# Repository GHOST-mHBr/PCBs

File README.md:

# How To Use
Just open your desired folder

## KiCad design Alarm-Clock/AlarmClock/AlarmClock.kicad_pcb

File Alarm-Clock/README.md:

# PCB for Alarm-Clock project
You can find source code [here](github.com/GHOST-mHBr/https://github.com/GHOST-mHBr/AVR-Codes/tree/master/Atmega8%20Async%20Timer2%20Standard%20C%20time%20API)

# 3D views of the final PCB
## Perspective View

## Front View

## Back View

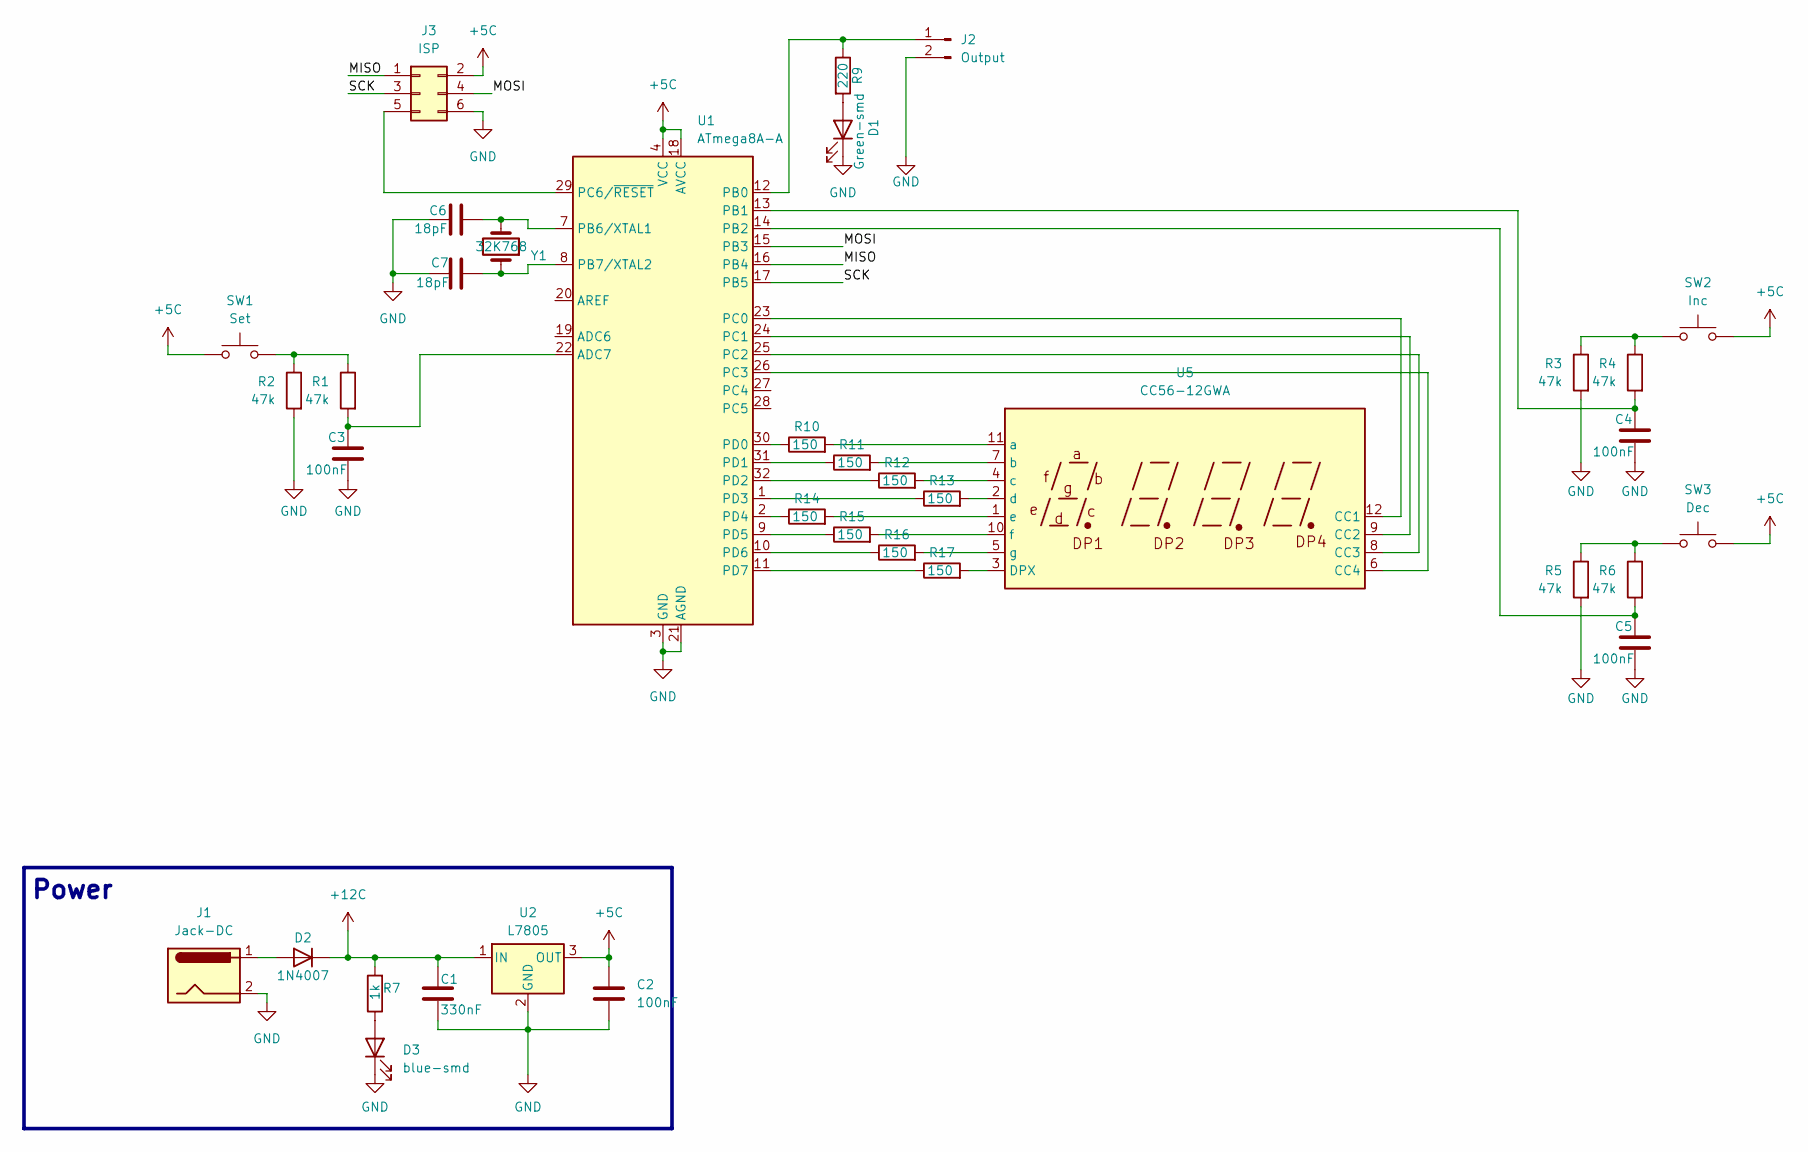
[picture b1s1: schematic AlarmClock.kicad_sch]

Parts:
C1: 330nF; C_0603_1608Metric
C2, C3, C4, C5: 100nF; C_0603_1608Metric
C6, C7: 18pF; C_0603_1608Metric
D1: Green-smd; LED_0805_2012Metric
D2: 1N4007; D_SMA
D3: blue-smd; LED_0603_1608Metric
J1: Jack-DC; BarrelJack_GCT_DCJ200-10-A_Horizontal
J2: Output; Molex_KK-254_AE-6410-02A_1x02_P2.54mm_Vertical
J3: ISP; IDC-Header_2x03_P2.54mm_Vertical
R1, R2, R3, R4, R5, R6: 47k; R_0603_1608Metric
R7: 1k; R_0603_1608Metric
R9: 220; R_0603_1608Metric
R10, R11, R12, R13, R14, R15, R16, R17: 150; R_0603_1608Metric
SW1: Set; Molex_KK-254_AE-6410-02A_1x02_P2.54mm_Vertical
SW2: Inc; Molex_KK-254_AE-6410-02A_1x02_P2.54mm_Vertical
SW3: Dec; Molex_KK-254_AE-6410-02A_1x02_P2.54mm_Vertical
U1: ATmega8A-A; TQFP-32_7x7mm_P0.8mm
U2: L7805; TO-220-3_Horizontal_TabDown
U5: CC56-12GWA
Y1: 32K768; Crystal_SMD_2012-2Pin_2.0x1.2mm

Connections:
+5C: C2.1, J3.2, SW1.1, SW2.1, SW3.1, U1.4 (VCC), U1.6 (VCC), U1.18 (AVCC), U2.3 (OUT)
+12C: C1.1, D2.1 (K), R7.2, U2.1 (IN)
/MISO: J3.1, U1.16 (PB4)
/MOSI: J3.4, U1.15 (PB3)
/SCK: J3.3, U1.17 (PB5)
GND: C1.2, C2.2, C3.2, C4.2, C5.2, C6.1, C7.1, D1.1 (K), D3.1 (K), J1.2, J2.2, J3.6, R2.2, R3.2, R5.2, U1.3 (GND), U1.5 (GND), U1.21 (AGND), U2.2 (GND)
unnamed: D1.2 (A), R9.2
unnamed: D2.2 (A), J1.1
unnamed: D3.2 (A), R7.1
unnamed: J2.1, R9.1, U1.12 (PB0)
unnamed: J3.5, U1.29 (PC6/~RESET)
unnamed: R1.1, R2.1, SW1.2
unnamed: R3.1, R4.1, SW2.2
unnamed: R5.1, R6.1, SW3.2
unnamed: C3.1, R1.2, U1.22 (ADC7)
unnamed: C4.1, R4.2, U1.13 (PB1)
unnamed: C5.1, R6.2, U1.14 (PB2)
unnamed: C6.2, U1.7 (PB6/XTAL1), Y1.2
unnamed: C7.2, U1.8 (PB7/XTAL2), Y1.1
unnamed: U1.23 (PC0), U5.12 (CC1)
unnamed: U1.24 (PC1), U5.9 (CC2)
unnamed: U1.25 (PC2), U5.8 (CC3)
unnamed: U1.26 (PC3), U5.6 (CC4)
unnamed: R10.1, U1.30 (PD0)
unnamed: R11.1, U1.31 (PD1)
unnamed: R12.1, U1.32 (PD2)
unnamed: R13.1, U1.1 (PD3)
unnamed: R14.1, U1.2 (PD4)
unnamed: R15.1, U1.9 (PD5)
unnamed: R16.1, U1.10 (PD6)
unnamed: R17.1, U1.11 (PD7)
unnamed: R17.2, U5.3 (DPX)
unnamed: R10.2, U5.11 (a)
unnamed: R11.2, U5.7 (b)
unnamed: R12.2, U5.4 (c)
unnamed: R13.2, U5.2 (d)
unnamed: R14.2, U5.1 (e)
unnamed: R15.2, U5.10 (f)
unnamed: R16.2, U5.5 (g)

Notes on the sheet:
Power

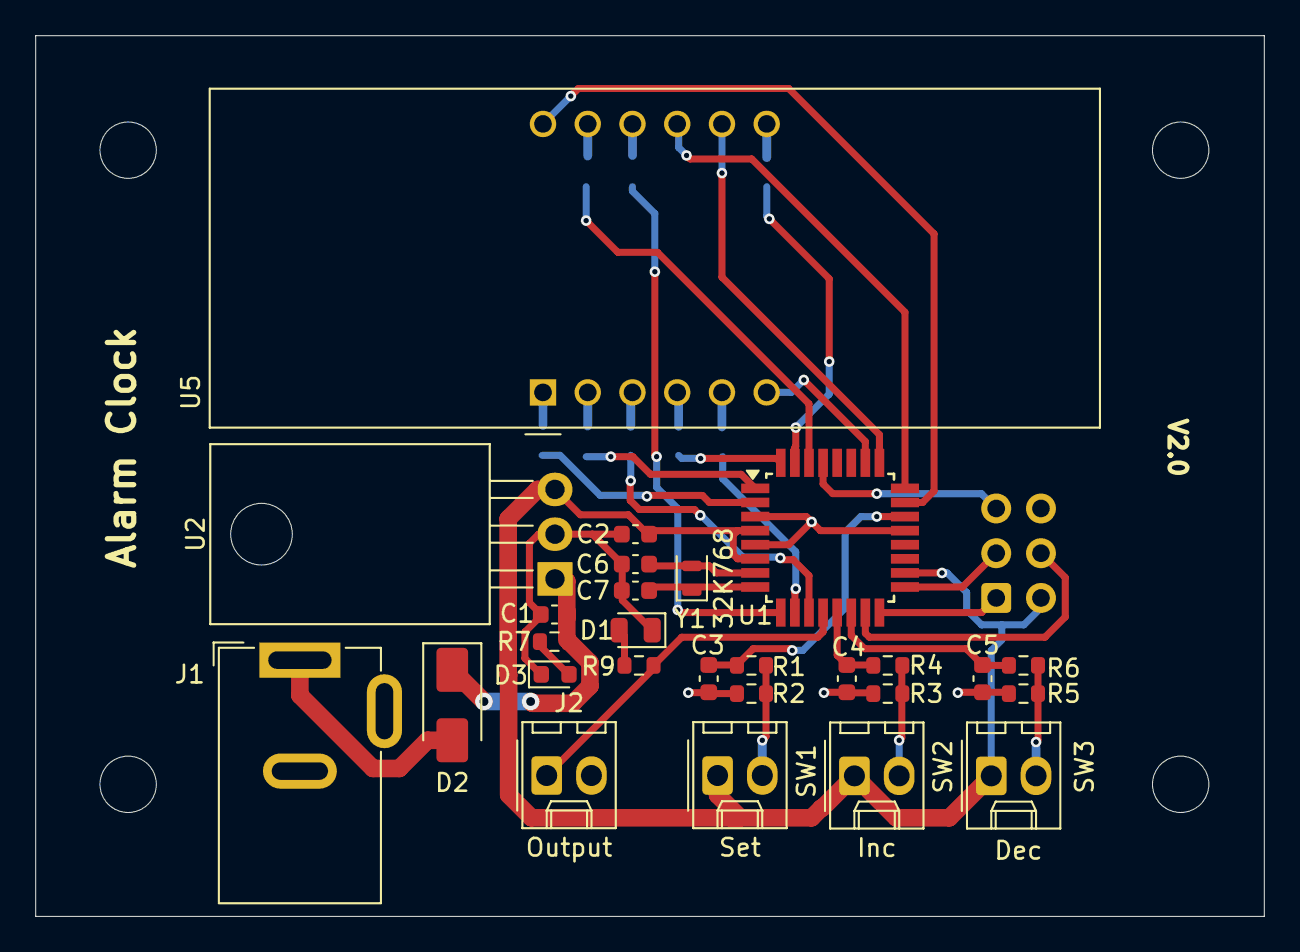
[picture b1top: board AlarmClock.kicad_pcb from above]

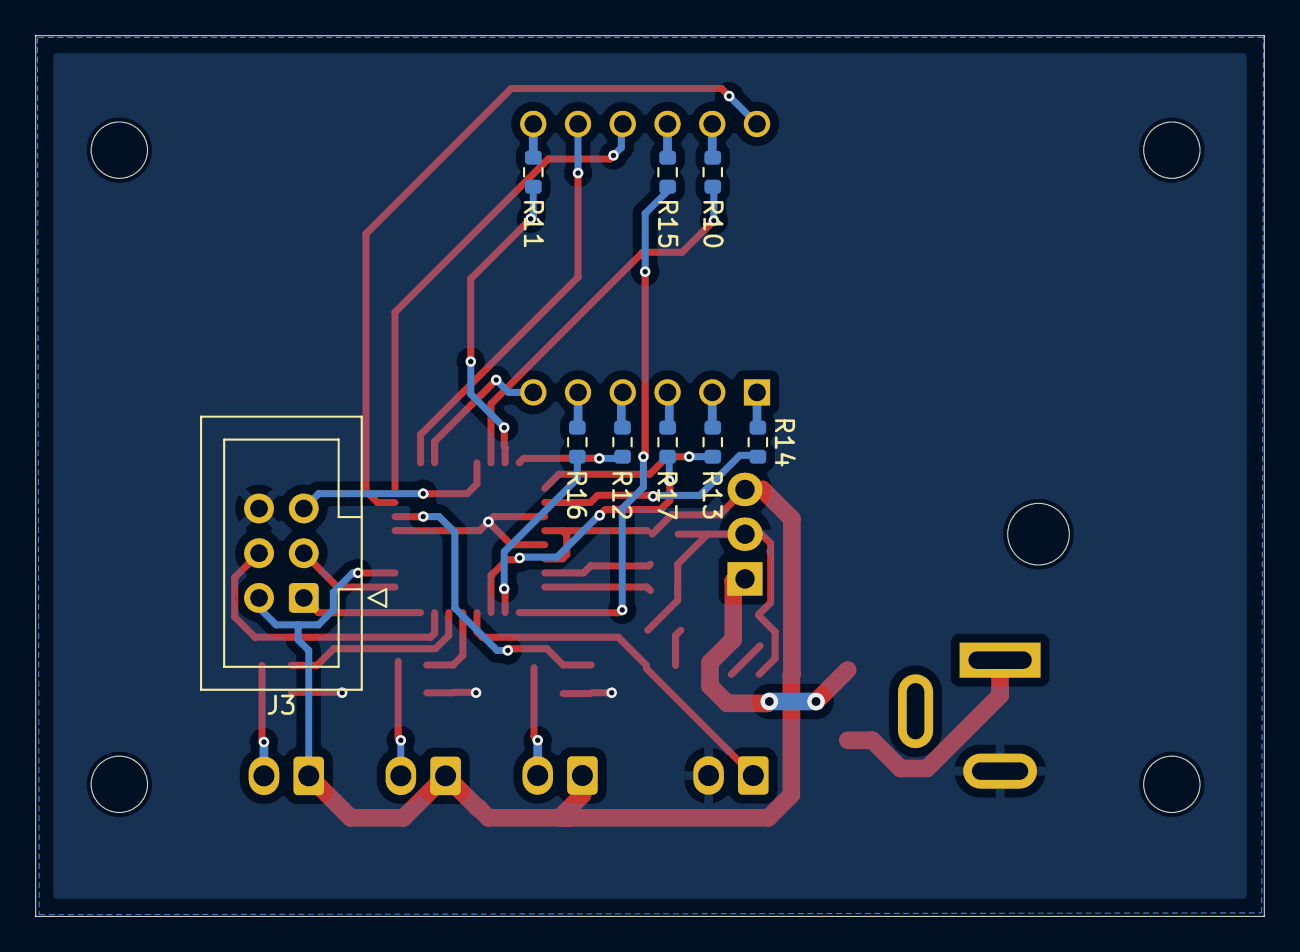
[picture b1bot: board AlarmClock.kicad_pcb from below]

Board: 2 copper layers, 69.8 x 50.0 mm, 36 parts (9 on the bottom side), 39 nets.

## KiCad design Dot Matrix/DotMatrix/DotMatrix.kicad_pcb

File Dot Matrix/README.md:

# PCB for 8x8 5mm bicolor(r/g) Dot Matrix Displays

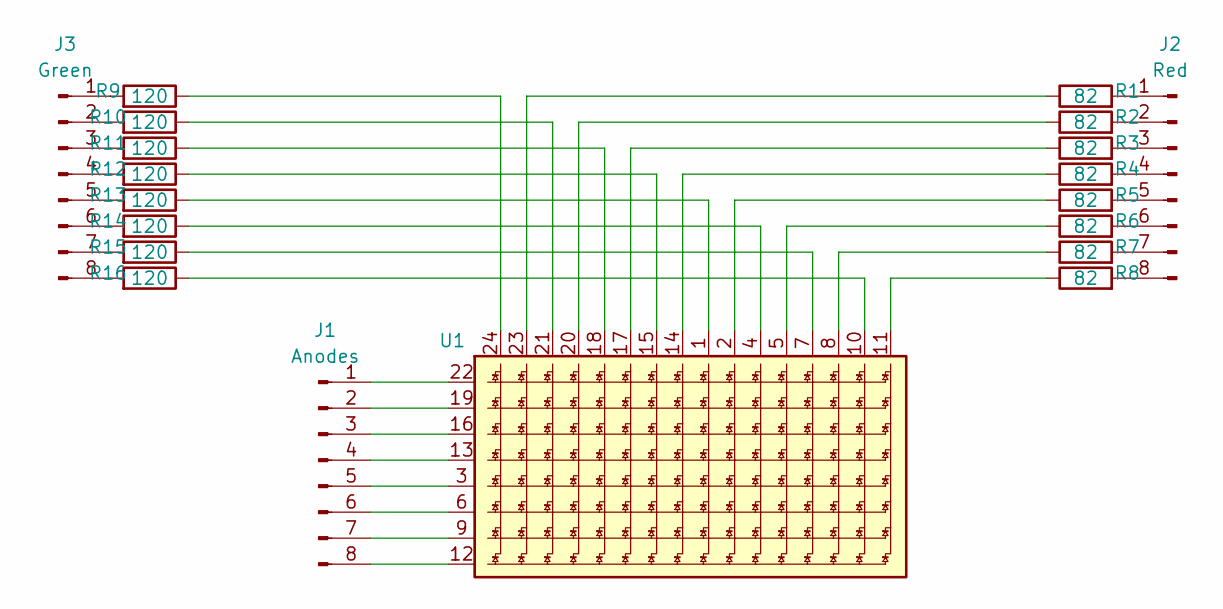
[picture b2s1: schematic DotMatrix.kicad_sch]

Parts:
J1: Anodes; PinHeader_1x08_P2.54mm_Vertical
J2: Red; PinHeader_1x08_P2.54mm_Vertical
J3: Green; PinHeader_1x08_P2.54mm_Vertical
R1, R2, R3, R4, R5, R6, R7, R8: 82; R_0603_1608Metric
R9, R10, R11, R12, R13, R14, R15, R16: 120; R_0603_1608Metric
U1: 8x8 5mm bicolor led dot matrix

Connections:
unnamed: J1.1, U1.22
unnamed: J1.2, U1.19
unnamed: J1.3, U1.16
unnamed: J1.4, U1.13
unnamed: J1.5, U1.3
unnamed: J1.6, U1.6
unnamed: J1.7, U1.9
unnamed: J1.8, U1.12
unnamed: J2.1, R1.2
unnamed: J2.2, R2.2
unnamed: J2.3, R3.2
unnamed: J2.4, R4.2
unnamed: J2.5, R5.2
unnamed: J2.6, R6.2
unnamed: J2.7, R7.2
unnamed: J2.8, R8.2
unnamed: J3.1, R9.2
unnamed: J3.2, R10.2
unnamed: J3.3, R11.2
unnamed: J3.4, R12.2
unnamed: J3.5, R13.2
unnamed: J3.6, R14.2
unnamed: J3.7, R15.2
unnamed: J3.8, R16.2
unnamed: R1.1, U1.23
unnamed: R2.1, U1.20
unnamed: R3.1, U1.17
unnamed: R4.1, U1.14
unnamed: R5.1, U1.2
unnamed: R6.1, U1.5
unnamed: R7.1, U1.8
unnamed: R8.1, U1.11
unnamed: R9.1, U1.24
unnamed: R10.1, U1.21
unnamed: R11.1, U1.18
unnamed: R12.1, U1.15
unnamed: R13.1, U1.1
unnamed: R14.1, U1.4
unnamed: R15.1, U1.7
unnamed: R16.1, U1.10

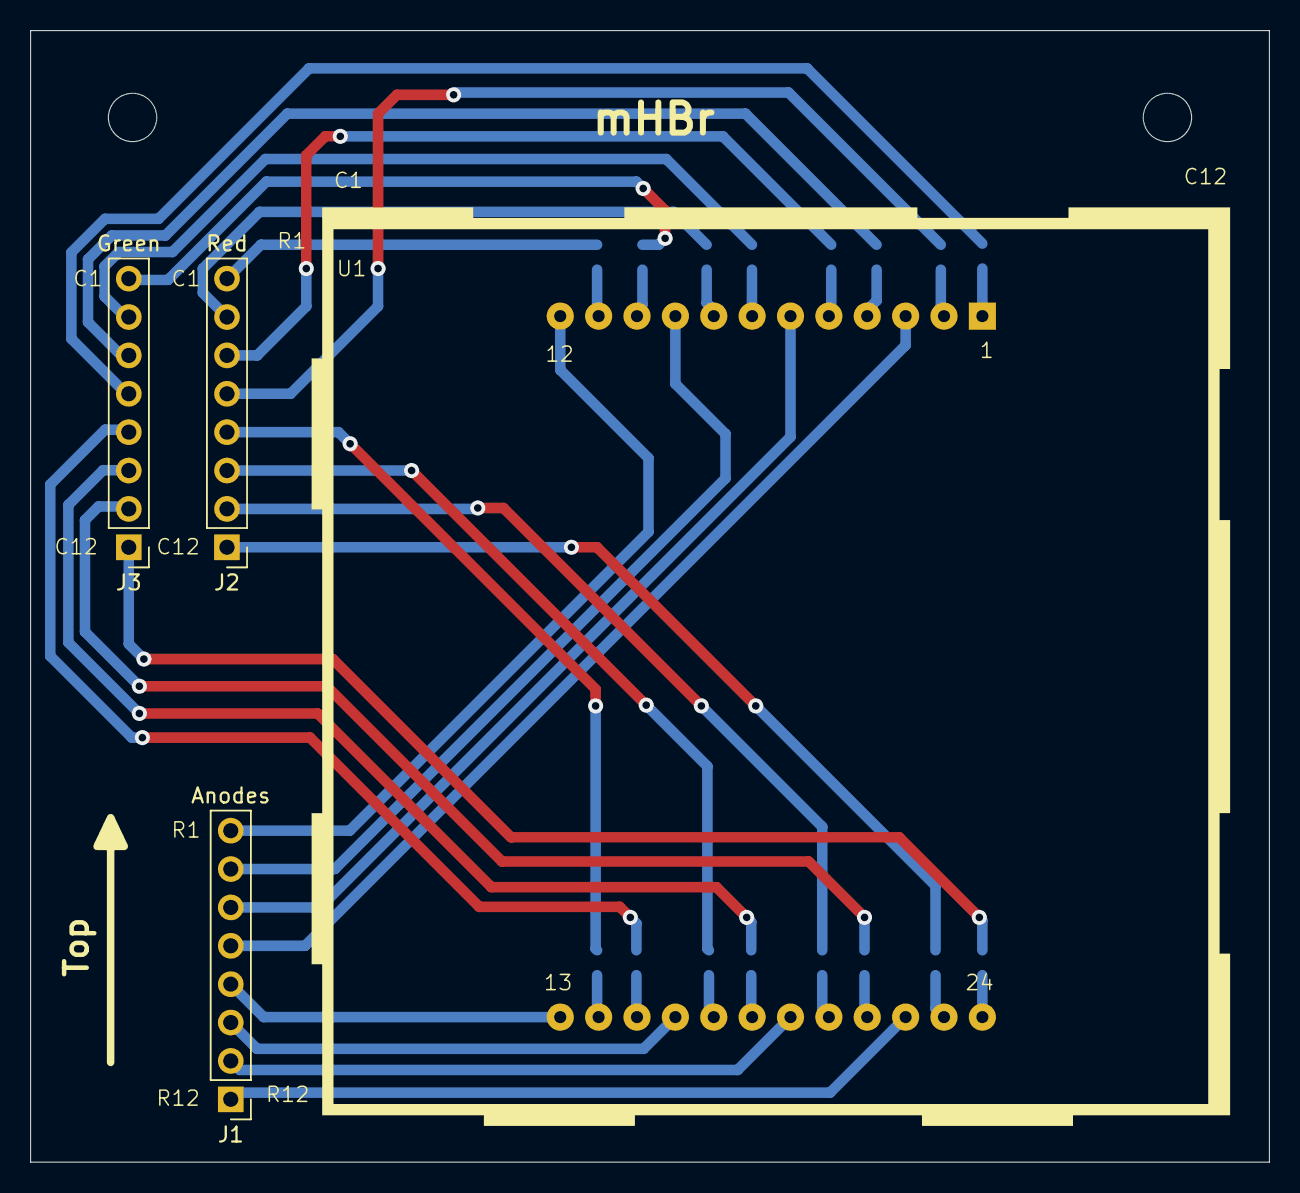
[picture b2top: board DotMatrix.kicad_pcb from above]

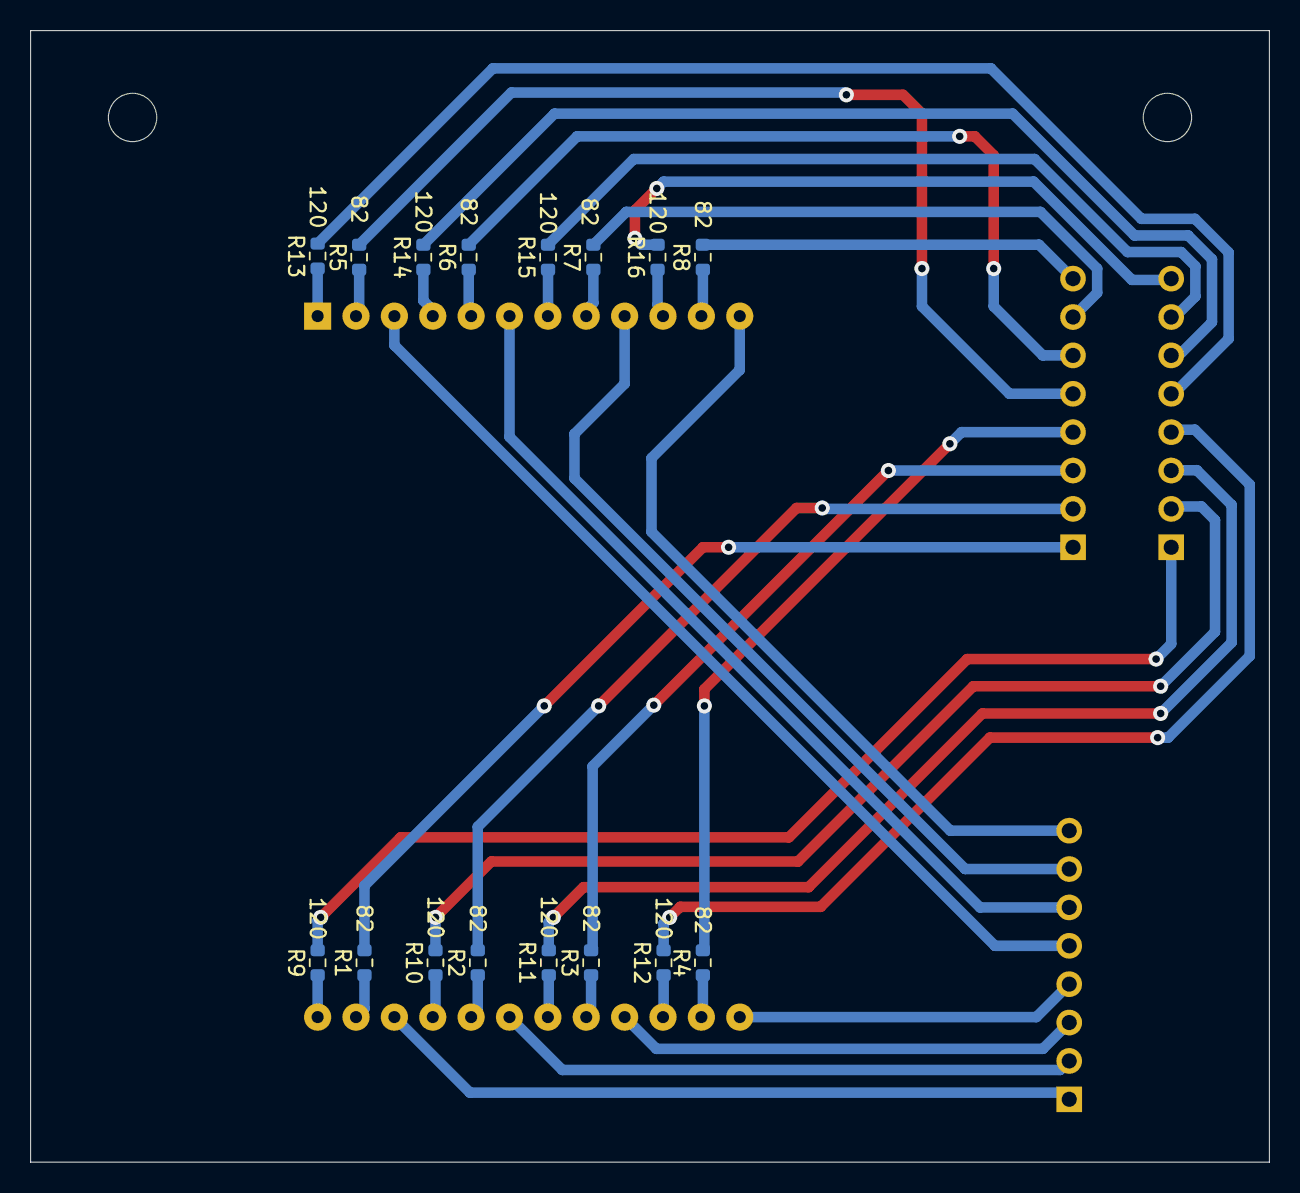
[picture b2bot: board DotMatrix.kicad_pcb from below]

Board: 2 copper layers, 82.0 x 74.9 mm, 20 parts (16 on the bottom side), 40 nets.

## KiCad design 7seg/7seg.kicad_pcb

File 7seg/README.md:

# PCB for 4-digit multiplexed CC 7-segments

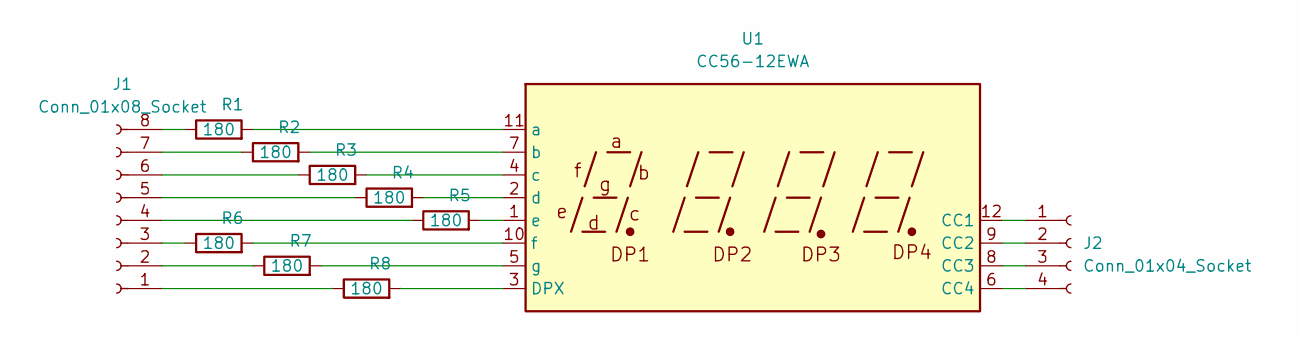
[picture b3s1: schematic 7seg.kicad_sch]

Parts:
J1: Conn_01x08_Socket; PinHeader_1x08_P2.54mm_Vertical
J2: Conn_01x04_Socket; PinHeader_1x04_P2.54mm_Vertical
R1, R2, R3, R4, R5, R6, R7, R8: 180; R_0603_1608Metric
U1: CC56-12EWA; CA56-12EWA

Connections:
unnamed: J1.1, R8.1
unnamed: J1.2, R7.1
unnamed: J1.3, R6.1
unnamed: J1.4, R5.1
unnamed: J1.5, R4.1
unnamed: J1.6, R3.1
unnamed: J1.7, R2.1
unnamed: J1.8, R1.1
unnamed: J2.1, U1.12 (CC1)
unnamed: J2.2, U1.9 (CC2)
unnamed: J2.3, U1.8 (CC3)
unnamed: J2.4, U1.6 (CC4)
unnamed: R8.2, U1.3 (DPX)
unnamed: R1.2, U1.11 (a)
unnamed: R2.2, U1.7 (b)
unnamed: R3.2, U1.4 (c)
unnamed: R4.2, U1.2 (d)
unnamed: R5.2, U1.1 (e)
unnamed: R6.2, U1.10 (f)
unnamed: R7.2, U1.5 (g)

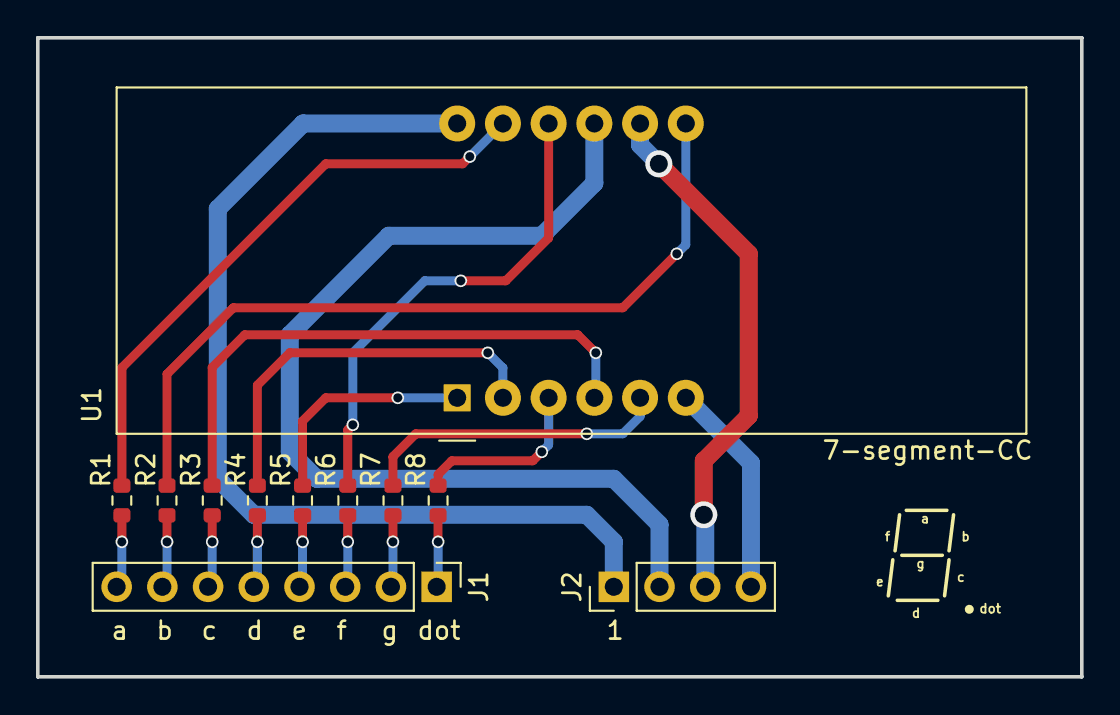
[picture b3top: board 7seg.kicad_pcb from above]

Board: 2 copper layers, 58.0 x 35.5 mm, 11 parts (0 on the bottom side), 20 nets.

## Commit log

2024-11-21 Adding READMEs
2024-11-25 Adding AlarmClock
2024-11-25 Adding pdf of schematic
2026-01-08 Fixing bugs
2026-01-08 Some cleanups
2026-02-06 Updating/Improving PCB. Adding ground plane, making crystal SMD, some alignments and cleanups. Adding missing crystal capacitors.
2026-02-06 Update README.md, adding PCB images
2026-02-06 Updating pcb images
